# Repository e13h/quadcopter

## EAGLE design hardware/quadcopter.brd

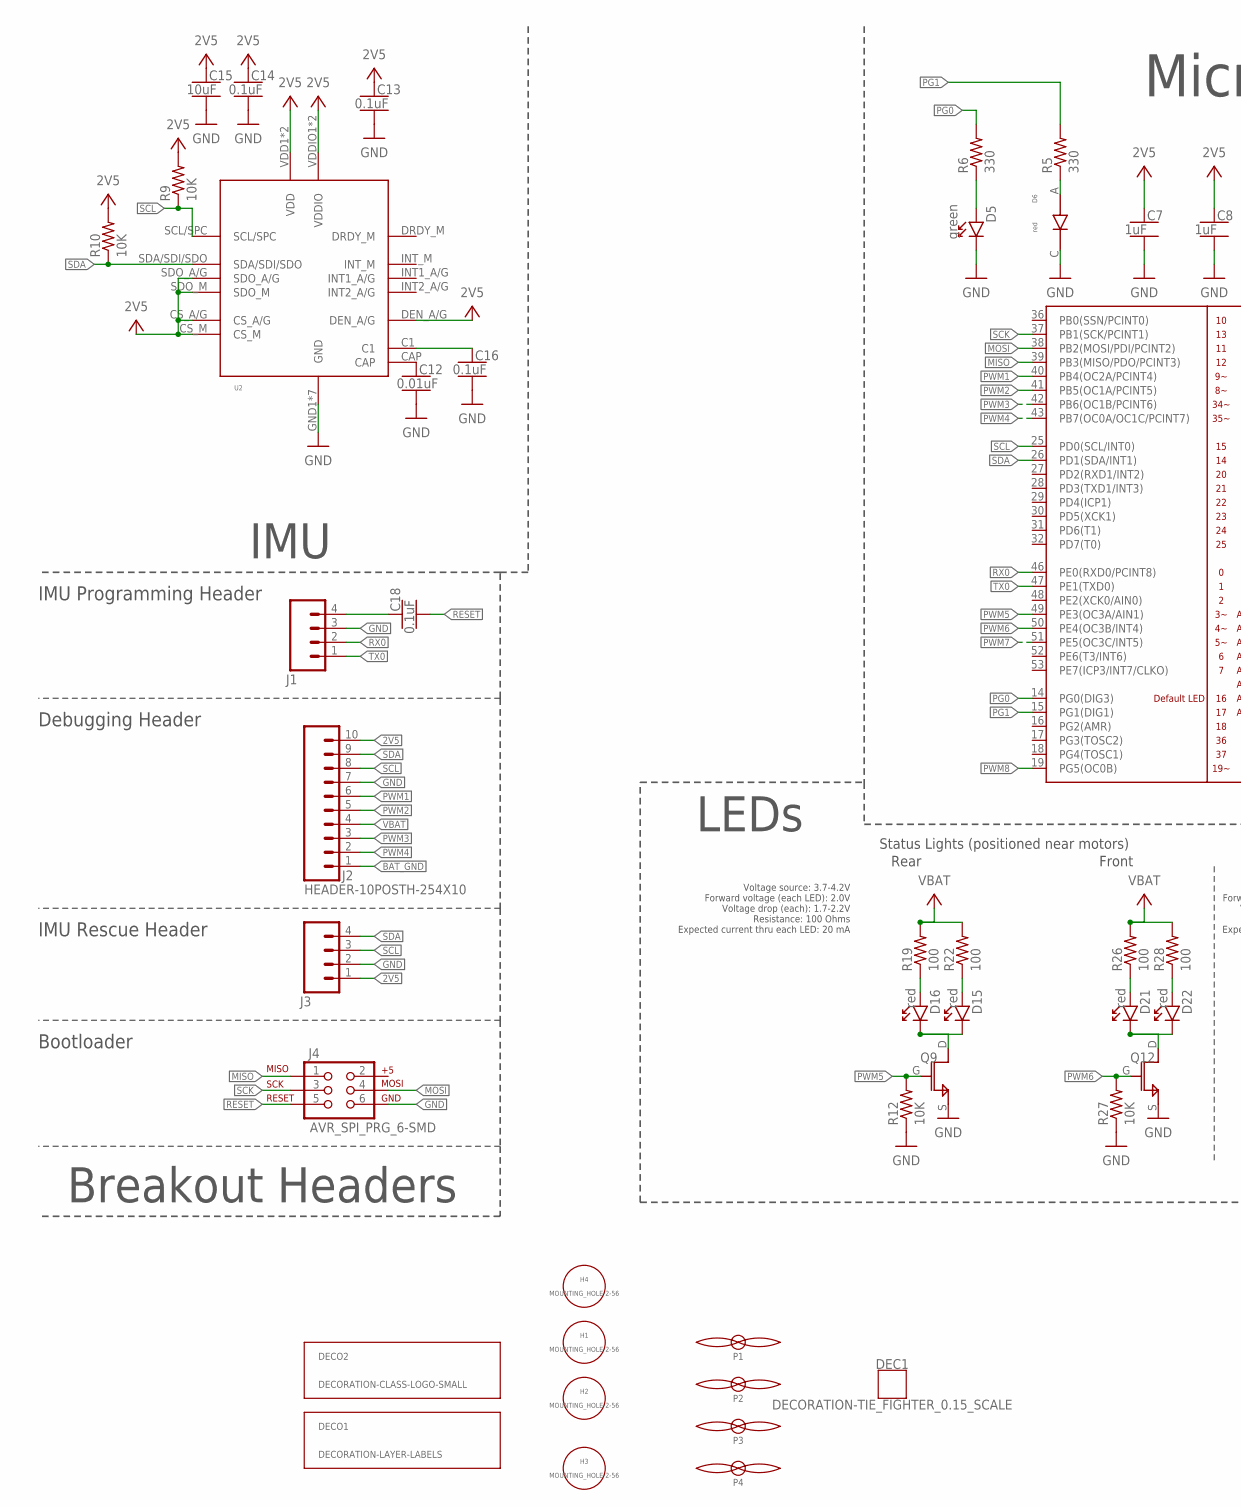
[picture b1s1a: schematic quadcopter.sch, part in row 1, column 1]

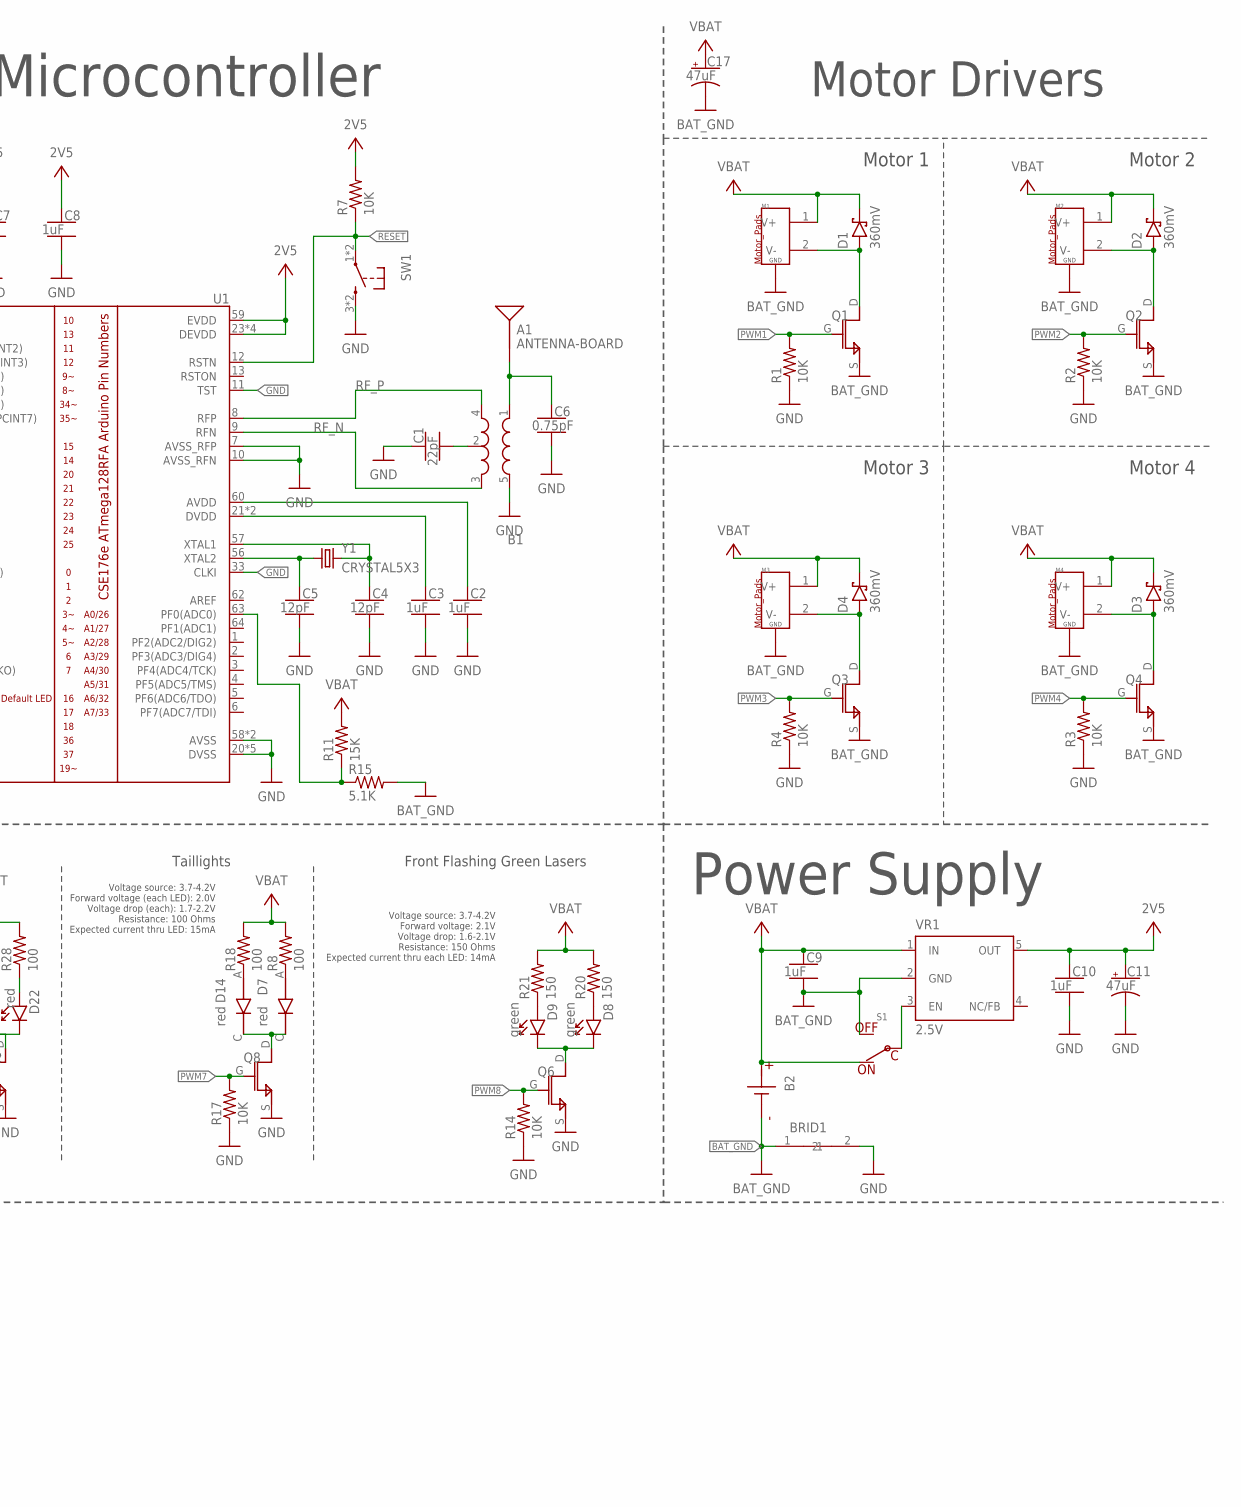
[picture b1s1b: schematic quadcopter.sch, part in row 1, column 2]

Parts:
A1: ANTENNA-BOARD; ANT_PCB_2.4GHZ_NRF8001_1.6MM_1OZ
B1: BALUN0805; BALUN
B2: BATTERY-SMD-TH; BATTERY-COMBO
BRID1: NET_BRIDGE_5X5
C1: 22pF; CAPC2012X140_HS
C2, C3, C7, C8, C9, C10: 1uF; CAPC2012X140_HS
C4, C5: 12pF; CAPC2012X140_HS
C6: 0.75pF; CAPC2012X140_HS
C11, C17: 47uF; CAPMP3216X180
C12: 0.01uF; CAPC2012X140_HS
C13, C14, C16, C18: 0.1uF; CAPC2012X140_HS
C15: 10uF; CAPC2012X140_HS
D1, D2, D3, D4: 360mV; SODFL3516X96
D5, D8, D9: green; LEDSC125X200X120-2_HS
D6, D7, D14: red; LTST-C170EKT
D15, D16, D21, D22: red; 1206_LED_REVERSE
DEC1: DECORATION-TIE_FIGHTER_0.15_SCALE; TIE_FIGHTER_0.15_SCALE
DECO1: DECORATION-LAYER-LABELS; LAYER_LABELS
DECO2: DECORATION-CLASS-LOGO-SMALL; QUADCLASS_LOGO_SMALL
H1, H2, H3, H4: MOUNTING_HOLE-2-56; 2-56-MOUNTING-HOLE-NO-METAL
J1: HEADER-4POS-0.1IN-FEMALE-SMD-BOTTOM-ENTRY; HEADER-1X4-BOTTOM-ENTRY
J2: HEADER-10POSTH-254X10; HDRV10W63P254_10X1_2540X254H838_HS
J3: HEADER-4POS-0.1IN-FEMALE; HDRVR4W80P254_1X4_1066X254X850B
J4: AVR_SPI_PRG_6-SMD; 2X3-SMD
M1, M2, M3, M4: MOTOR_PADS_GND-MOLEX-SMD; MOLEX-0532610271
P1, P2, P3, P4: PROPELLOR-45MM; MOTOR_AND_PROP
Q1, Q2, Q3, Q4, Q6, Q8, Q9, Q12: N-MOSFET-SI2302DS; SI2302DS
R1, R2, R3, R4, R7, R9, R10, R12, R14, R17, R27: 10K; RESC2012X60_HS
R5, R6: 330; RESC2012X60_HS
R8, R18, R19, R22, R26, R28: 100; RESC2012X60_HS
R11: 15K; RESC2012X60_HS
R15: 5.1K; RESC2012X60_HS
R20, R21: 150; RESC2012X60_HS
S1: POWER-SWITCH-MFS201N-9-Z-SMD-EDGE; JS102011SAQN
SW1: PUSHBUTTON_-4.5X4.5; 4.5MM_TACTILE_SWITCH_TL3305AF160QG
U1: ATMEGA128RFA1; QFN-64
U2: IMU_LSM9DS1-LSM9DS1; LSM9DS1
VR1: 2.5V; SOT23-DBV
Y1: CRYSTAL5X3; CRYSTAL-SMD-5X3

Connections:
2V5: C7.1, C8.1, C10.1, C11.1 (+), C13.1, C14.1, C15.1, J2.10, J3.1, R7.2, R9.2, R10.2, U1.23 (DEVDD), U1.34 (DEVDD), U1.44 (DEVDD), U1.54 (DEVDD), U1.59 (EVDD), U2.CS_A/G, U2.CS_M, U2.DEN_A/G, U2.SDO_A/G, U2.SDO_M, U2.VDD1 (VDD), U2.VDD2 (VDD), U2.VDDIO1 (VDDIO), U2.VDDIO2 (VDDIO), VR1.5 (OUT)
ANTENNA: A1.FEED, B1.1 (IN), C6.1
BAT_GND: B2.2 (N), B2.G (N), B2.G2 (N), B2.G3 (N), BRID1.1, C9.2, C17.2 (-), J2.1, M1.G1 (GND), M1.G2 (GND), M2.G1 (GND), M2.G2 (GND), M3.G1 (GND), M3.G2 (GND), M4.G1 (GND), M4.G2 (GND), Q1.S, Q2.S, Q3.S, Q4.S, R15.2, S1.A (OFF), VR1.2 (GND)
GND: B1.5 (GND), BRID1.2, C1.1, C2.2, C3.2, C4.2, C5.2, C6.2, C7.2, C8.2, C10.2, C11.2 (-), C12.2, C13.2, C14.2, C15.2, C16.2, D5.C, D6.C, J1.3, J2.7, J3.2, J4.6, Q6.S, Q8.S, Q9.S, Q12.S, R1.1, R2.1, R3.1, R4.1, R12.1, R14.1, R17.1, R27.1, SW1.3 (2), SW1.4 (2), U1.7 (AVSS_RFP), U1.10 (AVSS_RFN), U1.11 (TST), U1.20 (DVSS), U1.24 (DVSS), U1.33 (CLKI), U1.35 (DVSS), U1.45 (DVSS), U1.55 (DVSS), U1.58 (AVSS), U1.61 (AVSS), U2.GND1 (GND), U2.GND2 (GND), U2.RES1 (GND), U2.RES2 (GND), U2.RES3 (GND), U2.RES4 (GND), U2.RES5 (GND)
MISO: J4.1, U1.39 (PB3(MISO/PDO/PCINT3))
MOSI: J4.4, U1.38 (PB2(MOSI/PDI/PCINT2))
unnamed: D2.2 (A), M2.2 (V-), Q2.D
unnamed: D1.2 (A), M1.2 (V-), Q1.D
unnamed: D4.2 (A), M3.2 (V-), Q3.D
unnamed: D3.2 (A), M4.2 (V-), Q4.D
unnamed: D6.A, R5.1
unnamed: C18.1, J1.4
unnamed: B1.2 (GND), C1.2
unnamed: C2.1, U1.60 (AVDD)
unnamed: C3.1, U1.21 (DVDD), U1.22 (DVDD)
unnamed: C5.1, U1.56 (XTAL2), Y1.1
unnamed: C4.1, U1.57 (XTAL1), Y1.3 (2)
unnamed: D5.A, R6.1
unnamed: C12.1, U2.CAP
unnamed: D8.C, D9.C, Q6.D
unnamed: D14.A, R18.1
unnamed: D8.A, R20.1
unnamed: D9.A, R21.1
unnamed: D7.A, R8.1
unnamed: C16.1, U2.C1
unnamed: S1.C, VR1.3 (EN)
unnamed: D16.2 (A), R19.1
unnamed: D7.C, D14.C, Q8.D
unnamed: R11.1, R15.1, U1.63 (PF0(ADC0))
unnamed: D15.2 (A), R22.1
unnamed: D15.1 (C), D16.1 (C), Q9.D
unnamed: D21.1 (C), D22.1 (C), Q12.D
unnamed: D21.2 (A), R26.1
unnamed: D22.2 (A), R28.1
PG0: R6.2, U1.14 (PG0(DIG3))
PG1: R5.2, U1.15 (PG1(DIG1))
PWM1: J2.6, Q1.G, R1.2, U1.40 (PB4(OC2A/PCINT4))
PWM2: J2.5, Q2.G, R2.2, U1.41 (PB5(OC1A/PCINT5))
PWM3: J2.3, Q3.G, R4.2, U1.42 (PB6(OC1B/PCINT6))
PWM4: J2.2, Q4.G, R3.2, U1.43 (PB7(OC0A/OC1C/PCINT7))
PWM5: Q9.G, R12.2, U1.49 (PE3(OC3A/AIN1))
PWM6: Q12.G, R27.2, U1.50 (PE4(OC3B/INT4))
PWM7: Q8.G, R17.2, U1.51 (PE5(OC3C/INT5))
PWM8: Q6.G, R14.2, U1.19 (PG5(OC0B))
RESET: C18.2, J4.5, R7.1, SW1.1, SW1.2 (1), U1.12 (RSTN)
RF_N: B1.3 (OUT2), U1.9 (RFN)
RF_P: B1.4 (OUT1), U1.8 (RFP)
RX0: J1.2, U1.46 (PE0(RXD0/PCINT8))
SCK: J4.3, U1.37 (PB1(SCK/PCINT1))
SCL: J2.8, J3.3, R9.1, U1.25 (PD0(SCL/INT0)), U2.SCL/SPC
SDA: J2.9, J3.4, R10.1, U1.26 (PD1(SDA/INT1)), U2.SDA/SDI/SDO
TX0: J1.1, U1.47 (PE1(TXD0))
VBAT: B2.1, B2.P, C9.1, C17.1 (+), D1.1 (C), D2.1 (C), D3.1 (C), D4.1 (C), J2.4, M1.1 (V+), M2.1 (V+), M3.1 (V+), M4.1 (V+), R8.2, R11.2, R18.2, R19.2, R20.2, R21.2, R22.2, R26.2, R28.2, S1.B (ON), VR1.1 (IN)

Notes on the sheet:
Motor Drivers
Motor 1
Motor 2
Motor 3
Motor 4
IMU
Breakout Headers
IMU Programming Header
Debugging Header
IMU Rescue Header
Bootloader
Power Supply
Microcontroller
LEDs
Front Flashing Green Lasers
Status Lights (positioned near motors)
Voltage source: 3.7-4.2V Forward voltage: 2.1V Voltage drop: 1.6-2.1V Resistance: 150 Ohms Expected current thru each LED: 14mA
Voltage source: 3.7-4.2V Forward voltage (each LED): 2.0V Voltage drop (each): 1.7-2.2V Resistance: 100 Ohms Expected current thru each LED: 20 mA
Voltage source: 3.7-4.2V Forward voltage (each LED): 2.0V Voltage drop (each): 1.7-2.2V Resistance: 100 Ohms Expected current thru LED: 15mA
Taillights
Front
Rear

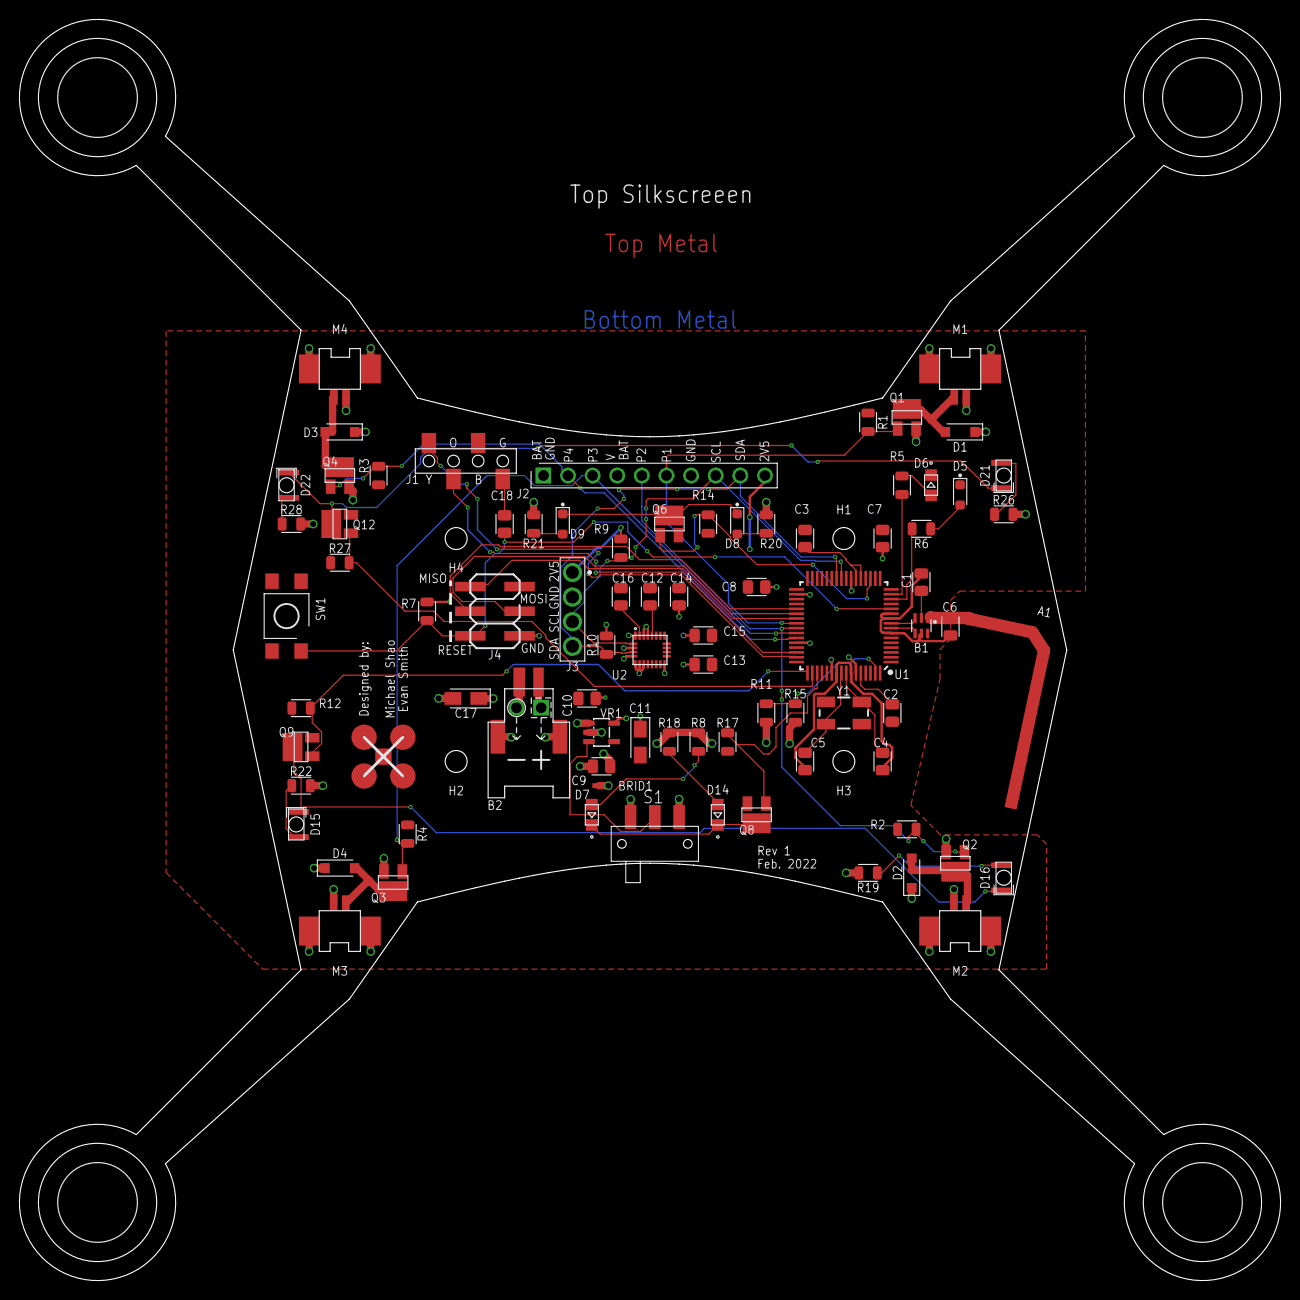
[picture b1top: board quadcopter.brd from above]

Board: 4 copper layers, 130.1 x 130.1 mm, 92 parts (0 on the bottom side), 53 nets.

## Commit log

2022-01-19 Running first quick check with what we have so far
2022-01-19 Replaced 3V3 with 2V5 and added GND to IMU cap pin
2022-01-19 Initial Submit
2022-01-20 Renamed parts that had $ symbols in them
2022-01-20 Updated attributes for net bridge
2022-01-20 Replace `quadparts_prebuilt` with `quadparts_prebuilt_2022`
2022-01-20 Use parts in local custom library
2022-01-20 Attempt to fix power supply to pass quick check
2022-01-20 Added LED library and sample ground effect LED to schematic
2022-01-20 Added datasheet for ground effects LED
2022-01-20 Named LED pads
2022-01-20 Moved LED device symbol to origin
2022-01-20 Added VBAT part to power supply
2022-01-20 Revisions
2022-01-20 Minor fixes
2022-01-20 minor fix 2
2022-01-20 Update custom library to latest version from Fusion
2022-01-20 Updated net bridge to reference local custom library file
2022-01-20 Added LED schematics
2022-01-20 Updated LED schematics and included voltage info
2022-01-20 Updated label sizes to match others
2022-01-20 Fixed 2V5 net on both sides of R15
2022-01-20 Wired some pins to GND and switch to BAT_GND for eaglint
2022-01-20 Reorient balun
2022-01-20 Wire decoupling cap between VBAT and BAT_GND
2022-01-20 Modify IMU decoupling caps
2022-01-20 Swap C1 and CAP caps in IMU
2022-01-20 Replaced `-SMD` variant battery with `-SMD-TH` variant
2022-01-22 Modify LED schematic to meet lab specs
2022-01-28 Board Commit
2022-01-28 Retrying the export process to run a quick check
2022-01-28 Updated the tie fighter decoration attributes
2022-01-28 Updated IMU pads and aligned parts to 0.5mm grid
2022-01-28 Updated quadparts_prebuilt_2022 library to latest version from class repo
2022-01-28 Replaced local refs to LED library with team versions
2022-01-28 Replaced local refs to `custom_michael_shao` lbr with team version
2022-01-28 Cleaned up `BAT_GND` traces
2022-01-28 Removed unnecessary LEDs
2022-01-29 Moved deregulating caps and fixed IMU metal cutouts
2022-01-29 Aligned net bridge to 0.5mm grid
2022-01-29 Starter code
2022-01-29 Code for reading the gimbals and printing to serial
2022-01-30 Fixed issues identified in human review
2022-01-30 Ignore `.vscode` directory
2022-01-31 Filled the pours 🤦🏼‍♂️
2022-01-31 Moved wires around near pwr switch so that throughhole touched gnd
2022-02-01 Callback for btn1
2022-02-01 Gimbal calibration code implemented
2022-02-01 Adds calibration mode into main loop
2022-02-01 Debug statements added
2022-02-01 Added code to make calibration more practical
2022-02-01 implements eeprom saving
2022-02-01 Define a struct
2022-02-01 Define some placeholder global vars for gimbals
2022-02-01 Add radio setup commands
2022-02-01 Flesh out functions to send, validate, and print a packet
2022-02-01 Move gimbal reading to separate function
2022-02-01 Create `set_gimbals` function to run in loop
2022-02-01 Move packet stuff to a separate library
2022-02-01 Change remote LCD backlight to reflect armed/disarmed mode
2022-02-01 Set constants with const
2022-02-01 Moved name for B2 out from under the part
2022-02-01 Adds packet retrieval
2022-02-01 Implemented basic quad update logic
2022-02-01 Allows for RC to get response
2022-02-01 Arming light works
2022-02-01 Getting the quadcopter to print out messages from the remote
2022-02-01 Only check for packets a few times a second
2022-02-02 Print gimbal poses every 100 ms
2022-02-02 Control motors with throttle gimbal
2022-02-02 Add shutoff if we don't get a packet
2022-02-02 Cleanup
2022-02-03 Quad refactor
2022-02-03 Allow remote reset sync
2022-02-03 Bug fixes
2022-02-03 Board review question file
2022-02-04 Questions so far
2022-02-04 Finished design review
2022-02-04 IMU clearance suggestion
2022-02-05 Add voltage divider comment and emails
2022-02-05 Added file with questions about our board
2022-02-07 Implementing changes from design review
2022-02-07 Replaced `-` with `_` in design review filepaths
2022-02-07 Move design review files to hardware dir
2022-02-07 Update LEDs to use latest lbr version
2022-02-08 Format whitespace for consistency
2022-02-11 Add board metadata for purchasing
2022-02-11 Add class logo, "created by" and date to the silkscreen
2022-02-11 Updated file structure to make eaglint happy
2022-02-11 Enable sensing and filtering (#11)
    * Copy in code from `ahrs_quad` example
    * Modify loop to check for packets every iteration
    * Encapsulate IMU printing to a function
    * Get the serial console working
    * Remove magnetometer setup
    * Remove unused global constant
2022-02-15 Use `EEPROM.update()` instead of `EEPROM.write()`
2022-02-15 Modify gain tuning with knob to be more modular
2022-02-15 Add PID loading, tuning, and saving
2022-02-15 Add failsafe in case eeprom loaded a nan
2022-02-15 Add comments to PID knob tuning
2022-02-15 Transmit the PID gains to the quad
2022-02-15 Clean up and standardize the plotting/printing functions
2022-02-15 Variable organization
2022-02-15 PID equation implemented
2022-02-15 Add simple mixer
2022-02-15 Update motor indexes
2022-02-15 Rename loop delta
2022-02-15 Update PID signature
2022-02-15 Incorporate PID control on pitch axis
2022-02-15 Add flag for printing motors to serial
2022-02-15 Constrain motor outputs
2022-02-15 Require throttle stick to be above 0 to move motors when armed
2022-02-15 Pass PID params by reference
2022-02-17 Invert yaw and pitch ranges (now they are correct)
2022-02-17 Prefix gimbal commands with `cmd_` for clarity
2022-02-17 Invert yaw and pitch requirements for arming
2022-02-17 Refactor to clean up global variables
2022-02-17 Update debug printing function to show more info
2022-02-17 Bugfix offset typo
2022-02-17 Drop packets if the magic constant doesn't match
2022-02-17 Remove integrator decay and set to 0 when throttle is 0
2022-02-17 Remove noisy serial print statement
2022-02-17 Added the start of yaw PID
2022-02-17 Set "armed" LED in main loop, not mixer
2022-02-17 Adds effective ceiling to throttle values
2022-02-17 Drop packets from the quad if the magic constant doesn't match
2022-02-17 Update LCD backlight states
2022-02-17 Minor adjustments
2022-02-17 Revert "Update LCD backlight states"
    This reverts commit 96b3db611c6db34442fb9aab4834e6e85b689034.
2022-02-17 Update gimbal calibration to use btn2 to end calibration
2022-02-17 Allow PID tuning for pitch, roll, and yaw axes
2022-02-17 Add magic constant back
2022-02-17 Add IMU flags to debugging to make it easier to view
2022-02-18 Update serial logger
2022-02-18 Use 115200 baud rate on remote
2022-02-18 Light up remote builtin LED too when armed
2022-02-18 Refactor gain tuning to be easier to read
2022-02-22 Modify gimbal centering on remote side
2022-02-22 Don't print "yaw filtered" since we don't run yaw through the filter
2022-02-22 Enable PID filter for yaw
2022-02-24 Center calibration and trim
2022-02-24 eeprom fix
2022-02-24 Set ODR to 238 Hz
2022-02-24 Cap throttle to 200 on remote side
2022-02-24 Incorporate gimbals into axis errors
2022-02-26 Calibrate the IMU the first time the quad is armed after power on
2022-02-26 Tweak IMU setup registers to improve responsiveness
2022-02-26 Fix mixer to correctly apply yaw PID and omit gimbal commands Gimbal commands are part of the input to the PID controller.
2022-02-26 Create dedicated trimming mode, break up calibration loop components
2022-02-26 Simplify debugging functions
2022-02-26 Standardize LCD updates Fix the bugs along the way.
2022-02-27 yaw tuning fix
2022-03-01 Move `deadband()` and `offset()` from quad to remote side
2022-03-01 Invert IMU roll rate (just like we did for pitch rate)
2022-03-01 Run PID for roll
2022-03-01 Invert roll and yaw commands
2022-03-03 Add some additional printing flags
2022-03-03 Better update timing
2022-03-03 Add a small decay to the I term in PID controller
2022-03-10 Clear the LCD on button presses
2022-03-10 Add flag for switching between FCB and custom quad
2022-03-13 Encapsulate logic for calculating offset angles for each axis
2022-03-13 Fix deadband to revert to axis centers instead of a constant value
2022-03-13 Remove noisy print statement
2022-03-13 Enable debug printing while in calibration mode
2022-03-13 Remove arbitrary cap on gimbal throttle
2022-03-13 Refresh LCD screen on all button presses
2022-03-13 Add a "real time mode" flag
2022-03-13 Flip pitch and yaw motor configuration
2022-03-13 Remove `capper` and simply constrain motor values I expect that this will help the quad behave just fine at medium to medium-high throttles, but may begin to behave unpredictably at full throttle.
2022-03-13 Add extra details to `print_gimbals()`
2022-03-14 Make the `BOARD_IS_FCB` flag true by default
2022-03-14 Set `BOARD_IS_FCB` to false (using custom quad)
2022-03-14 Un-invert the roll commands
2022-03-14 Add "max" throttle line to plotter when `FLAG_PRINT_MOTORS` is true
2022-03-14 Un-invert the yaw axis command
2022-03-14 Add PID "smoother"
2022-03-14 Constrain gimbal commands to stay within bounds of their data types
2022-03-14 Set some debug flags to false by default
2022-03-14 Quad acknowledges when remote is disarmed during setup and enters loop
2022-03-14 Disarm the remote after 10 seconds of inactivity when throttle is 0
2022-03-14 Use unsigned longs when working with `millis()` That's what `millis()` returns.
2022-03-14 Only set armed state to false when looking at pkt from quad The remote should only be able to enter "armed" state when gimbals are down and out. Also, remove `millis() % x == 0` from if-statement
2022-03-14 Use `update_time()` to handle debug print statements
2022-03-15 Send motor values from quad to remote
2022-03-15 Flip some values for FCB
2022-03-15 Add method for constraining motors
2022-03-15 Simplify PID smoother
2022-03-15 Reduce range of motion for more stable flight
2022-03-16 Add loop time printing
2022-03-16 Only set the cursor when necessary (expensive operation apparently)
2022-03-16 Update debug time only every 100 ms
2022-03-16 Use a throttle gimbal max of 240
2022-03-16 Get rid of decay on integral term
2022-03-16 Comment out PID smoothing for now It seems to hurt more than it helps, but needs more testing
2022-03-16 Tune PID coefficients in increments of 0.01 instead of 0.05
2022-08-29 tweaks from the last day of class
